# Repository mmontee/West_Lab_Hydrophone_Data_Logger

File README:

**West Lab Hydrophone Data Logger**

The West Lab Hydrophone Data Logger uses a Teensy 4.0 and the Teensy Audio shield to periodically record audio data.

See the user manual for more information.

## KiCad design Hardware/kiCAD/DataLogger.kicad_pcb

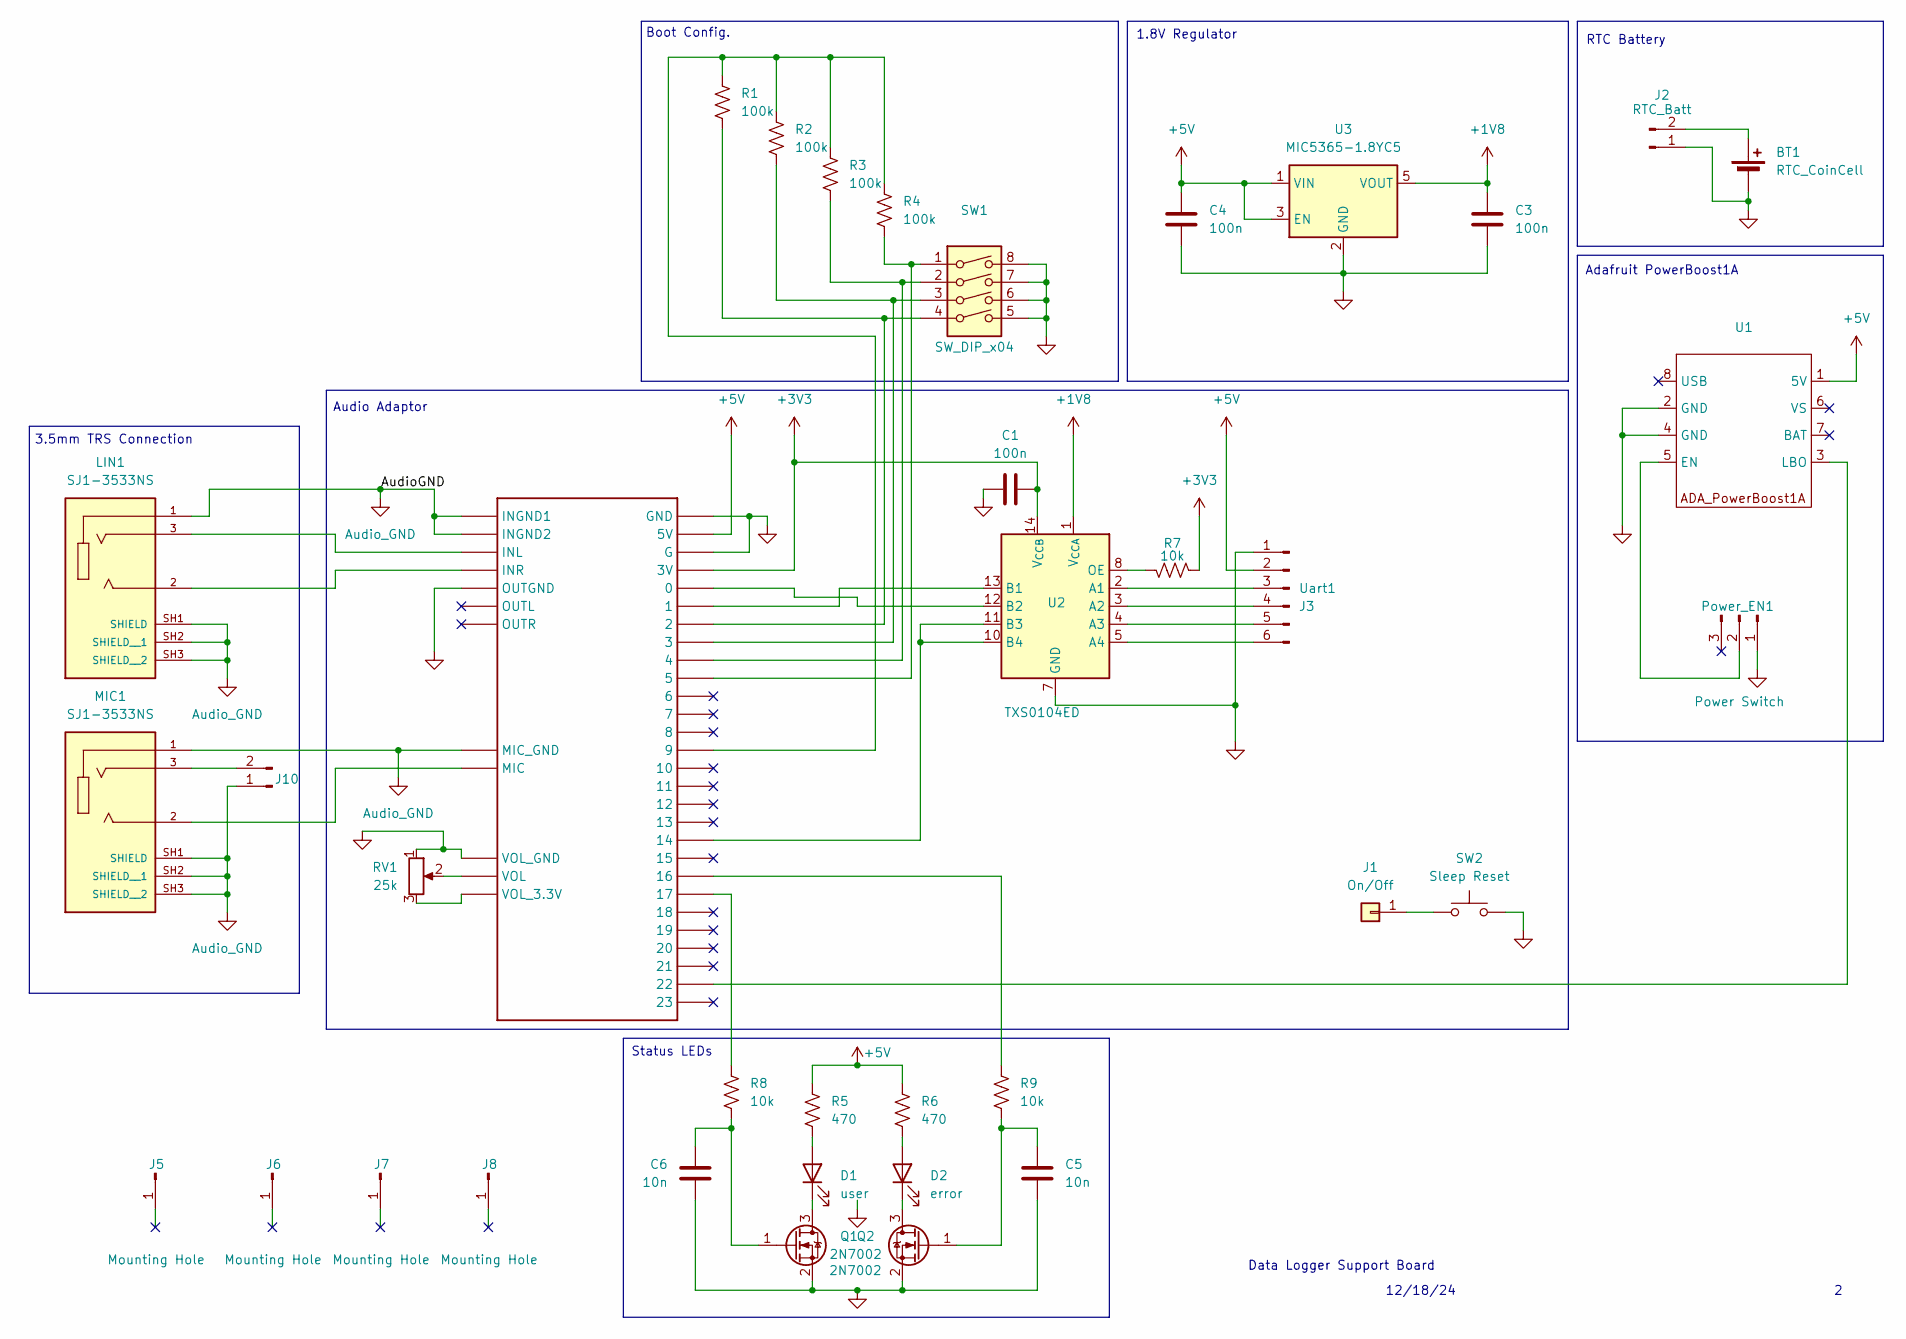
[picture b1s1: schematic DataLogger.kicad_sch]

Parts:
BT1: RTC_CoinCell; BatteryHolder_Keystone_3034_1x20mm
C1, C3, C4: 100n; C_0805_2012Metric_Pad1.18x1.45mm_HandSolder
C5, C6: 10n; C_0805_2012Metric_Pad1.18x1.45mm_HandSolder
D1: user; LED_0805_2012Metric_Pad1.15x1.40mm_HandSolder
D2: error; LED_0805_2012Metric_Pad1.15x1.40mm_HandSolder
J1: On/Off; PinSocket_1x01_P2.54mm_Vertical
J2: RTC_Batt; PinHeader_1x02_P2.54mm_Vertical
J3: Uart1; PinHeader_1x06_P2.54mm_Vertical
J5, J6, J7, J8: Mounting Hole; MountingHole_3.2mm_M3_Pad_Via
J10: Conn_01x02_Pin; SolderJumper-2_P1.3mm_Open_RoundedPad1.0x1.5mm
LIN1: SJ1-3533NS; CUI_SJ1-3533NS; PARTREV 1.04
MIC1: SJ1-3533NS; CUI_SJ1-3533NS; PARTREV 1.04
Power_EN1: Power Switch; SW_CK_JS202011CQN_DPDT_Straight
Q1, Q2: 2N7002; SOT-23
R1, R2, R3, R4: 100k; R_0805_2012Metric_Pad1.20x1.40mm_HandSolder
R5, R6: 470; R_0805_2012Metric_Pad1.20x1.40mm_HandSolder
R7, R8, R9: 10k; R_0805_2012Metric_Pad1.20x1.40mm_HandSolder
RV1: 25k
SW1: SW_DIP_x04; DIP8_208-4_CTS
SW2: Sleep Reset; SW_SPST_PTS647_Sx38
T1: AUDIOSHIELD
U1: ADA_powerBoost1A
U2: TXS0104ED; SOIC-14_3.9x8.7mm_P1.27mm
U3: MIC5365-1.8YC5; SOT-353_SC-70-5

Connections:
+1V8: C3.2, U2.1 (V_{CCA}), U3.5 (VOUT)
+3V3: C1.2, R7.1, T1.3V, U2.14 (V_{CCB})
+5V: C4.1, J3.2, R5.1, R6.1, T1.5V, U1.1 (5V), U3.1 (VIN), U3.3 (EN)
Audio_GND: J10.1, LIN1.1, LIN1.SH1 (SHIELD), LIN1.SH2 (SHIELD__1), LIN1.SH3 (SHIELD__2), MIC1.1, MIC1.SH1 (SHIELD), MIC1.SH2 (SHIELD__1), MIC1.SH3 (SHIELD__2), T1.GND_MIC (MIC_GND), T1.INGND1, T1.INGND2
GND: BT1.2 (-), C1.1, C3.1, C4.2, C5.1, C6.1, J2.1, J3.1, Power_EN1.1, Q1.2 (S), Q2.2 (S), RV1.1, SW1.5, SW1.6, SW1.7, SW1.8, SW2.2, T1.G, T1.GND, T1.OUTGND, T1.VOL_GND, U1.2 (GND), U1.4 (GND), U2.7 (GND), U3.2 (GND)
unnamed: BT1.1 (+), J2.2
unnamed: D1.2 (A), R5.2
unnamed: D1.1 (K), Q1.3 (D)
unnamed: D2.2 (A), R6.2
unnamed: D2.1 (K), Q2.3 (D)
unnamed: J1.1, SW2.1
unnamed: J3.3, U2.2 (A1)
unnamed: J3.4, U2.3 (A2)
unnamed: J3.5, U2.4 (A3)
unnamed: J3.6, U2.5 (A4)
unnamed: J10.2, MIC1.3
unnamed: LIN1.2, T1.INR
unnamed: LIN1.3, T1.INL
unnamed: MIC1.2, T1.MIC
unnamed: Power_EN1.2, U1.5 (EN)
unnamed: C6.2, Q1.1 (G), R8.2
unnamed: C5.2, Q2.1 (G), R9.2
unnamed: R1.1, R2.1, R3.1, R4.1, T1.9
unnamed: R1.2, SW1.4, T1.2
unnamed: R2.2, SW1.3, T1.3
unnamed: R3.2, SW1.2, T1.4
unnamed: R4.2, SW1.1, T1.5
unnamed: R8.1, T1.17
unnamed: R9.1, T1.16
unnamed: RV1.2, T1.VOL
unnamed: RV1.3, T1.VOL_3.3V
unnamed: T1.22, U1.3 (LBO)
unnamed: T1.1, U2.13 (B1)
unnamed: T1.0, U2.12 (B2)
unnamed: T1.14, U2.10 (B4), U2.11 (B3)
unnamed: R7.2, U2.8 (OE)

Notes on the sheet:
Status LEDs
3.5mm TRS Connection
12/18/24
Adafruit PowerBoost1A
RTC Battery
Audio Adaptor
Boot Config.
1.8V Regulator
Data Logger Support Board

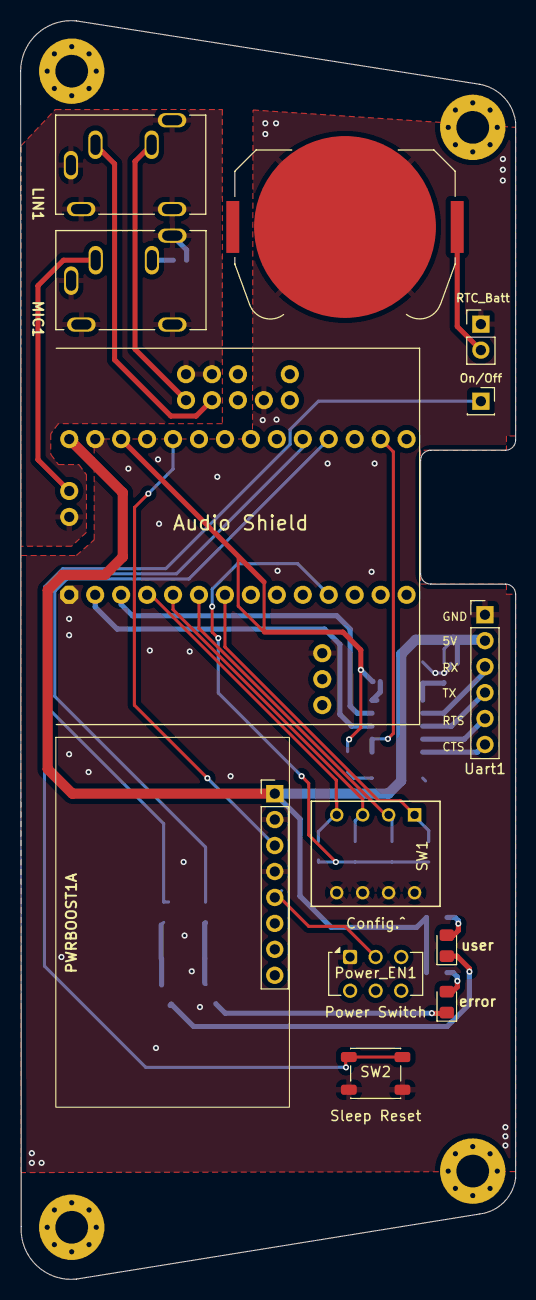
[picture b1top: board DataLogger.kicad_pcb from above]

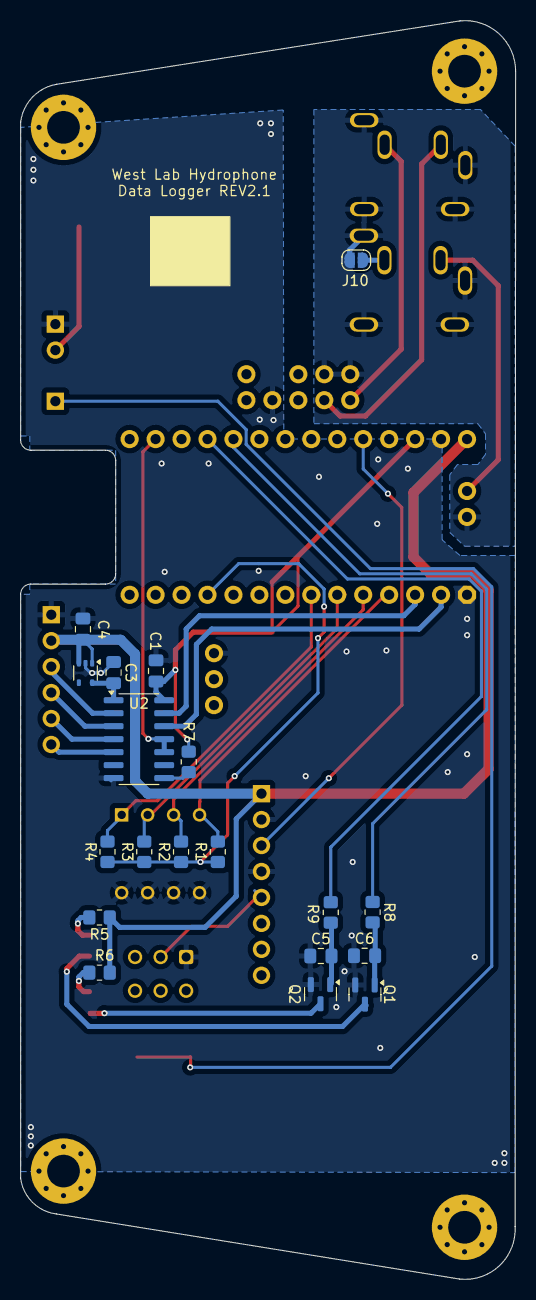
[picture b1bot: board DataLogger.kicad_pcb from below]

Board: 2 copper layers, 48.4 x 123.2 mm, 36 parts (19 on the bottom side), 34 nets.

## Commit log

2025-01-05 Create folder
2025-01-05 KiCAD Project upload
2025-01-05 REV1
2025-01-06 Rename Hydrophone Data Logger User Manual.md to README
2025-01-07 update to manual
2025-01-08 BOM upload
2025-01-08 Rename West Lab Hydrophone Data Logger Bom - Sheet1.pdf to West Lab Hydrophone Data Logger Bom .pdf
2025-01-30 Update user manual
2025-03-14 .py added, software readme added
2025-04-19 Rev2 Hardware
2025-04-27 TXS0104ED wiring fix and layout adjustments for improved SD card access. REV2.1
